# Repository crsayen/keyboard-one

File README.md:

### A little disclaimer

This is the first keyboard I built from scratch -- I layed out the PCB, designed the case, and configured the firmware. The PCB design isn't great, the case is OK, the firmware is in a sort of *if it ain't broke, don't fix it* state, and it will probably stay that way.

I do plan on sharing more designs as I build them. As of Nov 2022, I have a wireless version of this board with 10 or 12 columns, and a partially wireless split keyboard (the halves are connected via USB-C) using a single XIAO controller. I've got PCBs on order for both, and I will share once I've built and validated those designs. 

# keyboard one

I've included a `.hex` file you can flash to your board. It is Vial compatible and it's what I'm using. There is also a `.vil` file which is my keymap. You can load it using the Vial app.

I've also included everything I have for this board from my local qmk but there is no guarantee it's going to work. I got it to the point where I could edit my keymap with the Vial app and stopped there as that's all I really need.

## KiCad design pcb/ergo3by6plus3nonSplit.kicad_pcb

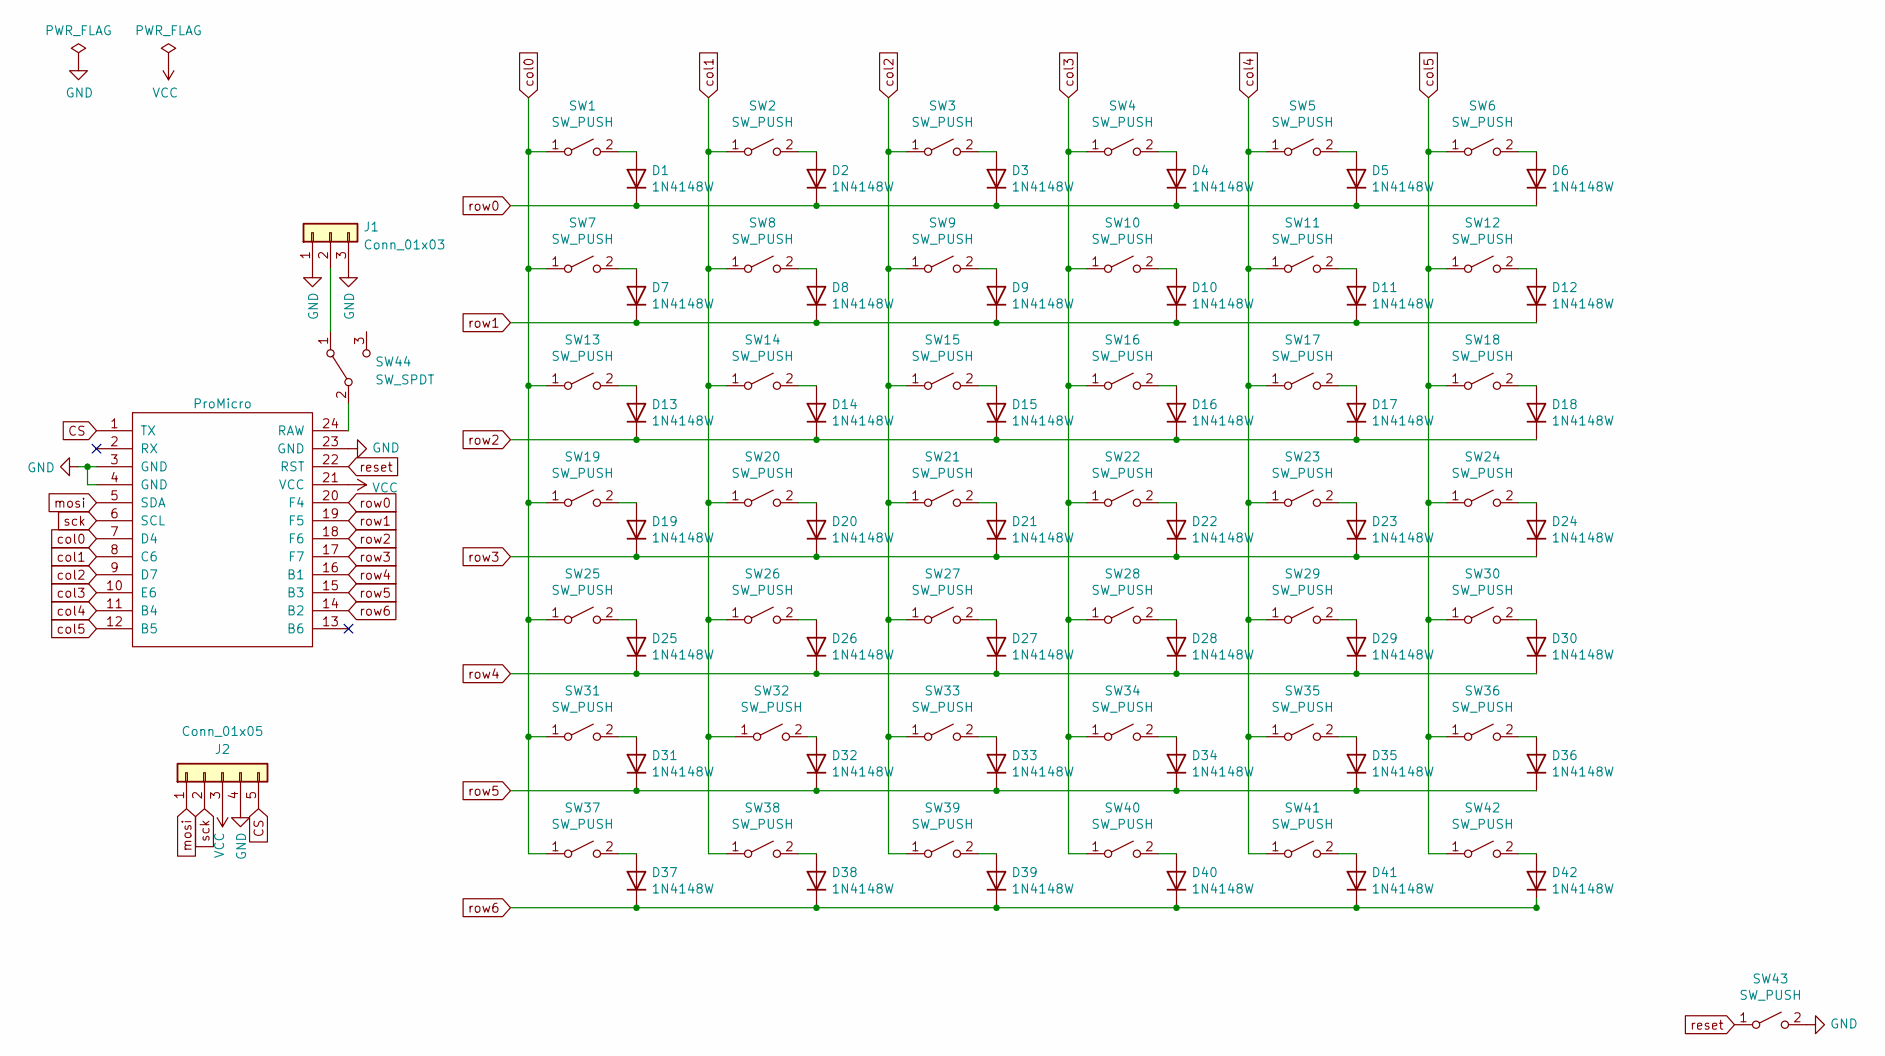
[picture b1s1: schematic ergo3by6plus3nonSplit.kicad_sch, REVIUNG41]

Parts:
A1: ProMicro; ProMicro-EnforcedTop
D1, D2, D3, D4, D5, D6, D7, D8, D9, D10, D11, D12, D13, D14, D15, D16, D17, D18, D19, D20, D21, D22, D23, D24, D25, D26, D27, D28, D29, D30, D31, D32, D33, D34, D35, D36, D37, D38, D39, D40, D41, D42: 1N4148W; D_SOD-123
J1: Conn_01x03; JST_PH_S3B-PH-SM4-TB_1x03-1MP_P2.00mm_Horizontal
J2: Conn_01x05; PinHeader_1x05_P2.54mm_Vertical
SW1, SW2, SW3, SW4, SW5, SW6, SW7, SW8, SW9, SW10, SW11, SW12, SW13, SW14, SW15, SW16, SW17, SW18, SW19, SW20, SW21, SW22, SW23, SW24, SW25, SW26, SW27, SW28, SW29, SW30, SW31, SW32, SW33, SW34, SW35, SW36, SW37, SW38, SW41, SW42: SW_PUSH; SW_Hotswap_Kailh_MX_1.00u
SW39, SW40: SW_PUSH; SW_Hotswap_Kailh_MX_1.25u_90deg
SW43: SW_PUSH; SW_SPST_PTS645
SW44: SW_SPDT; CUS-12TB

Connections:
GND: A1.3 (GND), A1.4 (GND), A1.23 (GND), J1.1, J1.3, J2.4, SW43.2 (B)
LED: A1.1 (TX), J2.5
unnamed: A1.5 (SDA), J2.1
unnamed: A1.6 (SCL), J2.2
unnamed: A1.24 (RAW), SW44.2 (B)
unnamed: D1.2 (A), SW1.2 (B)
unnamed: D2.2 (A), SW2.2 (B)
unnamed: D3.2 (A), SW3.2 (B)
unnamed: D4.2 (A), SW4.2 (B)
unnamed: D5.2 (A), SW5.2 (B)
unnamed: D6.2 (A), SW6.2 (B)
unnamed: D7.2 (A), SW7.2 (B)
unnamed: D8.2 (A), SW8.2 (B)
unnamed: D9.2 (A), SW9.2 (B)
unnamed: D10.2 (A), SW10.2 (B)
unnamed: D11.2 (A), SW11.2 (B)
unnamed: D12.2 (A), SW12.2 (B)
unnamed: D13.2 (A), SW13.2 (B)
unnamed: D14.2 (A), SW14.2 (B)
unnamed: D15.2 (A), SW15.2 (B)
unnamed: D16.2 (A), SW16.2 (B)
unnamed: D17.2 (A), SW17.2 (B)
unnamed: D18.2 (A), SW18.2 (B)
unnamed: D19.2 (A), SW19.2 (B)
unnamed: D20.2 (A), SW20.2 (B)
unnamed: D21.2 (A), SW21.2 (B)
unnamed: D22.2 (A), SW22.2 (B)
unnamed: D23.2 (A), SW23.2 (B)
unnamed: D24.2 (A), SW24.2 (B)
unnamed: D25.2 (A), SW25.2 (B)
unnamed: D26.2 (A), SW26.2 (B)
unnamed: D27.2 (A), SW27.2 (B)
unnamed: D28.2 (A), SW28.2 (B)
unnamed: D29.2 (A), SW29.2 (B)
unnamed: D30.2 (A), SW30.2 (B)
unnamed: D31.2 (A), SW31.2 (B)
unnamed: D32.2 (A), SW32.2 (B)
unnamed: D33.2 (A), SW33.2 (B)
unnamed: D34.2 (A), SW34.2 (B)
unnamed: D35.2 (A), SW35.2 (B)
unnamed: D36.2 (A), SW36.2 (B)
unnamed: D37.2 (A), SW37.2 (B)
unnamed: D38.2 (A), SW38.2 (B)
unnamed: D39.2 (A), SW39.2 (B)
unnamed: D40.2 (A), SW40.2 (B)
unnamed: D41.2 (A), SW41.2 (B)
unnamed: D42.2 (A), SW42.2 (B)
unnamed: J1.2, SW44.1 (A)
VCC: A1.21 (VCC), J2.3
col0: A1.7 (D4), SW1.1 (A), SW7.1 (A), SW13.1 (A), SW19.1 (A), SW25.1 (A), SW31.1 (A), SW37.1 (A)
col1: A1.8 (C6), SW2.1 (A), SW8.1 (A), SW14.1 (A), SW20.1 (A), SW26.1 (A), SW32.1 (A), SW38.1 (A)
col2: A1.9 (D7), SW3.1 (A), SW9.1 (A), SW15.1 (A), SW21.1 (A), SW27.1 (A), SW33.1 (A), SW39.1 (A)
col3: A1.10 (E6), SW4.1 (A), SW10.1 (A), SW16.1 (A), SW22.1 (A), SW28.1 (A), SW34.1 (A), SW40.1 (A)
col4: A1.11 (B4), SW5.1 (A), SW11.1 (A), SW17.1 (A), SW23.1 (A), SW29.1 (A), SW35.1 (A), SW41.1 (A)
col5: A1.12 (B5), SW6.1 (A), SW12.1 (A), SW18.1 (A), SW24.1 (A), SW30.1 (A), SW36.1 (A), SW42.1 (A)
reset: A1.22 (RST), SW43.1 (A)
row0: A1.20 (F4), D1.1 (K), D2.1 (K), D3.1 (K), D4.1 (K), D5.1 (K), D6.1 (K)
row1: A1.19 (F5), D7.1 (K), D8.1 (K), D9.1 (K), D10.1 (K), D11.1 (K), D12.1 (K)
row2: A1.18 (F6), D13.1 (K), D14.1 (K), D15.1 (K), D16.1 (K), D17.1 (K), D18.1 (K)
row3: A1.17 (F7), D19.1 (K), D20.1 (K), D21.1 (K), D22.1 (K), D23.1 (K), D24.1 (K)
row4: A1.16 (B1), D25.1 (K), D26.1 (K), D27.1 (K), D28.1 (K), D29.1 (K), D30.1 (K)
row5: A1.15 (B3), D31.1 (K), D32.1 (K), D33.1 (K), D34.1 (K), D35.1 (K), D36.1 (K)
row6: A1.14 (B2), D37.1 (K), D38.1 (K), D39.1 (K), D40.1 (K), D41.1 (K), D42.1 (K)

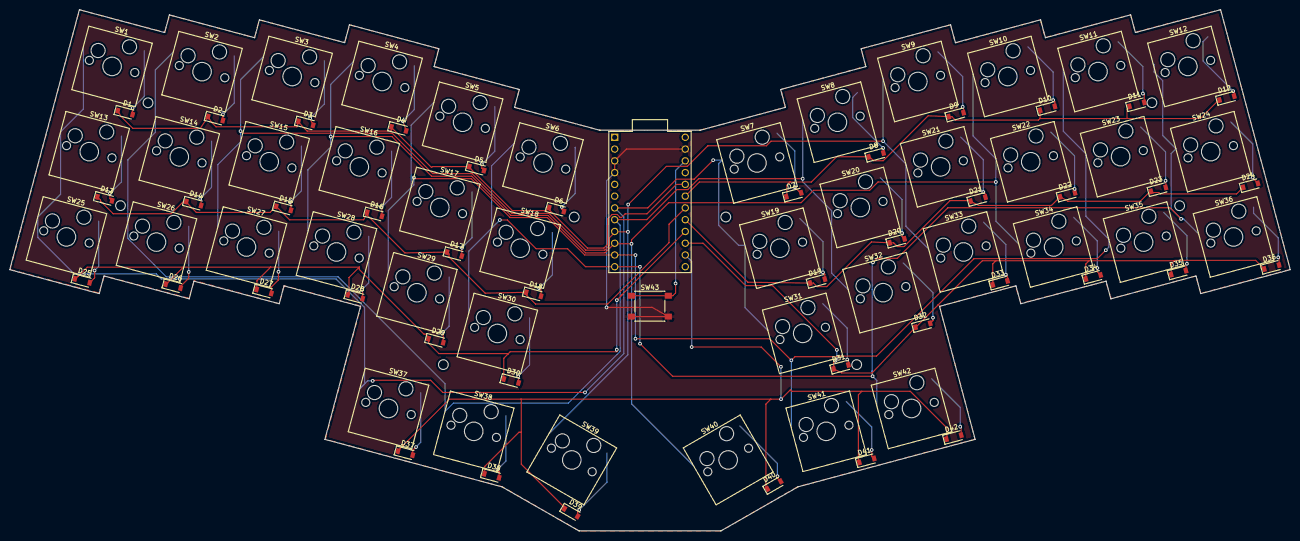
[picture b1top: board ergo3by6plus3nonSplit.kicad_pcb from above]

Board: 2 copper layers, 276.5 x 112.5 mm, 86 parts (0 on the bottom side), 57 nets.

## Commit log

2022-10-21 init
2022-10-21 rm *bak
2022-10-21 Create LICENSE
2022-11-21 updated models
2022-11-21 add firmware stuff
2022-11-21 add readme
2022-11-21 add picture
2022-11-21 maybe fix broken link?
2022-11-21 add another picture. didnt realize the last one was missing top and keys
2022-11-21 add another picture... part 2
